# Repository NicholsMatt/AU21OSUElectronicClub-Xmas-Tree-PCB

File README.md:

# AU21OSUElectronicClub Xmas Tree PCB
 Circuit board Christmas trees for the OSU Electronics Club!

 https://www.youtube.com/watch?v=kueU6unH_6Y&t=53s

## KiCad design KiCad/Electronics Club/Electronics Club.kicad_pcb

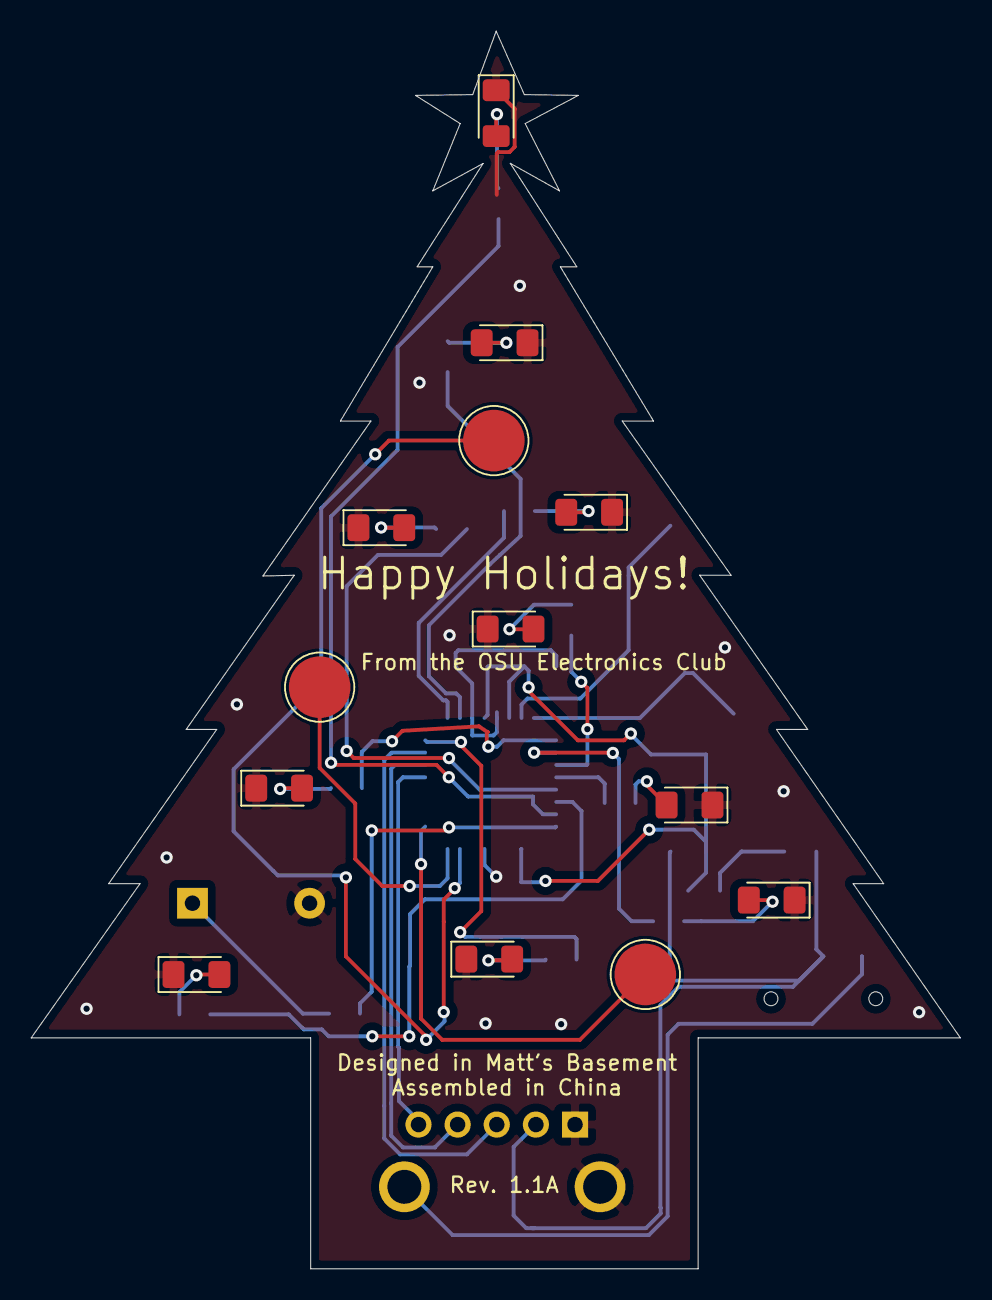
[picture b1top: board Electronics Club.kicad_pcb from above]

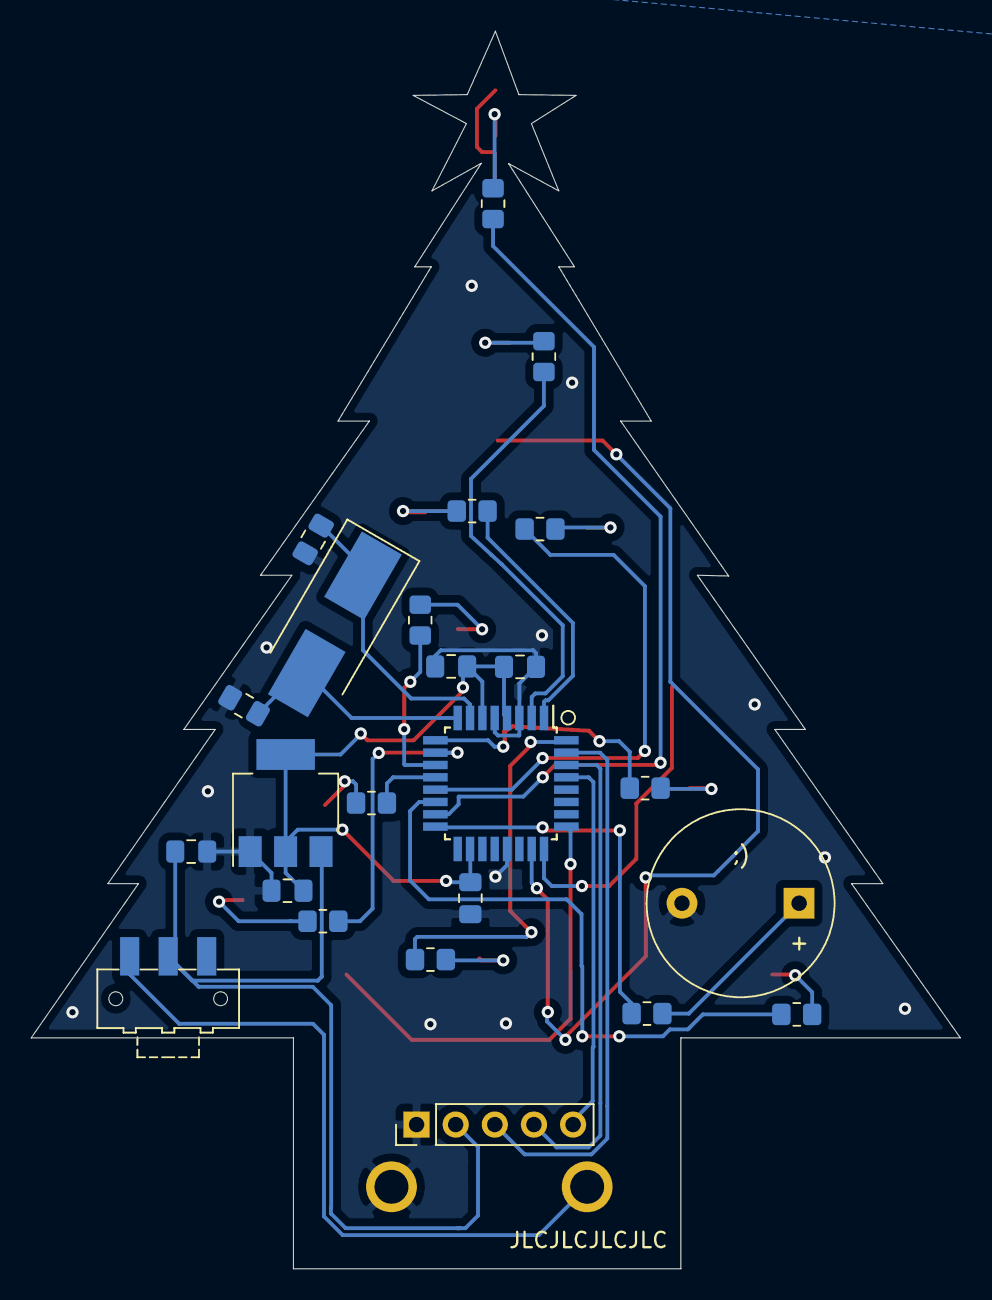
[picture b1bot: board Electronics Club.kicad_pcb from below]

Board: 2 copper layers, 60.3 x 80.3 mm, 38 parts (25 on the bottom side), 34 nets.

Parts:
BT1: 9V Battery; 9V Snap
BZ1: Buzzer; Buzzer_12x9.5RM7.6
C1, C3, C4, C5: 1uF; C_0805_2012Metric_Pad1.18x1.45mm_HandSolder
C2: 4.7uF; C_0805_2012Metric_Pad1.18x1.45mm_HandSolder
C6, C7: 18pF; C_0805_2012Metric_Pad1.18x1.45mm_HandSolder
D1: STAR_LED; LED_1206_3216Metric_Pad1.42x1.75mm_HandSolder
D2, D3, D4: LED_Y; LED_1206_3216Metric_Pad1.42x1.75mm_HandSolder
D5, D6: LED_R; LED_1206_3216Metric_Pad1.42x1.75mm_HandSolder
D7, D8: LED_G; LED_1206_3216Metric_Pad1.42x1.75mm_HandSolder
D9, D10: LED_B; LED_1206_3216Metric_Pad1.42x1.75mm_HandSolder
J1: Conn_01x05_Female; PinHeader_1x05_P2.54mm_Vertical
R1, R2, R3, R4, R11: 100; R_0805_2012Metric_Pad1.20x1.40mm_HandSolder
R5, R6: 1k; R_0805_2012Metric_Pad1.20x1.40mm_HandSolder
R7, R8: 4.7k; R_0805_2012Metric_Pad1.20x1.40mm_HandSolder
R9, R10: 330; R_0805_2012Metric_Pad1.20x1.40mm_HandSolder
SW1: Power Switch; SW_SPDT_CK-JS102011SAQN
TP1, TP2, TP3: TestPoint; TestPoint_Pad_D4.0mm
U2: LD1117S50TR_SOT223; SOT-223-3_TabPin2
U3: ATmega328P-AU; TQFP-32_7x7mm_P0.8mm
Y1: 16MHz; Crystal_SMD_7050-2Pin_7.0x5.0mm_HandSoldering

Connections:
+5V: C2.1, C3.1, C4.1, C5.1, U2.2, U3.4, U3.6, U3.18
/328_RX: J1.4, U3.30
/328_TX: J1.3, U3.31
/D2: R10.1, U3.32
/D3: R9.1, U3.1
/D4: R8.1, U3.2
/D5: R7.1, U3.9
/D6: R6.1, U3.10
/D7: R5.1, U3.11
/D8: R4.1, U3.12
/D9: R3.1, U3.13
/D10: R2.1, U3.14
/D11MOSI: R1.1, U3.15
/D12MISO: R11.1, U3.16
/D14: TP1.1, U3.23
/D15: TP2.1, U3.24
/D16: TP3.1, U3.25
/RESET: J1.5, U3.29
GND: BT1.2, BZ1.2, C1.2, C2.2, C3.2, C4.2, C5.2, C6.1, C7.1, D1.1, D2.1, D3.1, D4.1, D5.1, D6.1, D7.1, D8.1, D9.1, D10.1, J1.1, U2.1, U3.3, U3.5, U3.21
unnamed: BT1.1, SW1.1
unnamed: BZ1.1, R11.2
unnamed: C6.2, U3.7, Y1.1
unnamed: C7.2, U3.8, Y1.2
unnamed: D1.2, R1.2
unnamed: D2.2, R2.2
unnamed: D3.2, R3.2
unnamed: D4.2, R4.2
unnamed: D5.2, R5.2
unnamed: D6.2, R6.2
unnamed: D7.2, R7.2
unnamed: D8.2, R8.2
unnamed: D9.2, R9.2
unnamed: D10.2, R10.2
VCC: C1.1, J1.2, SW1.2, U2.3

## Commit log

2021-11-24 Added all the files
2021-11-26 Added arduino code
2021-11-27 More code
2021-11-29 Major revision
2021-11-29 Generated paste files for stencil
